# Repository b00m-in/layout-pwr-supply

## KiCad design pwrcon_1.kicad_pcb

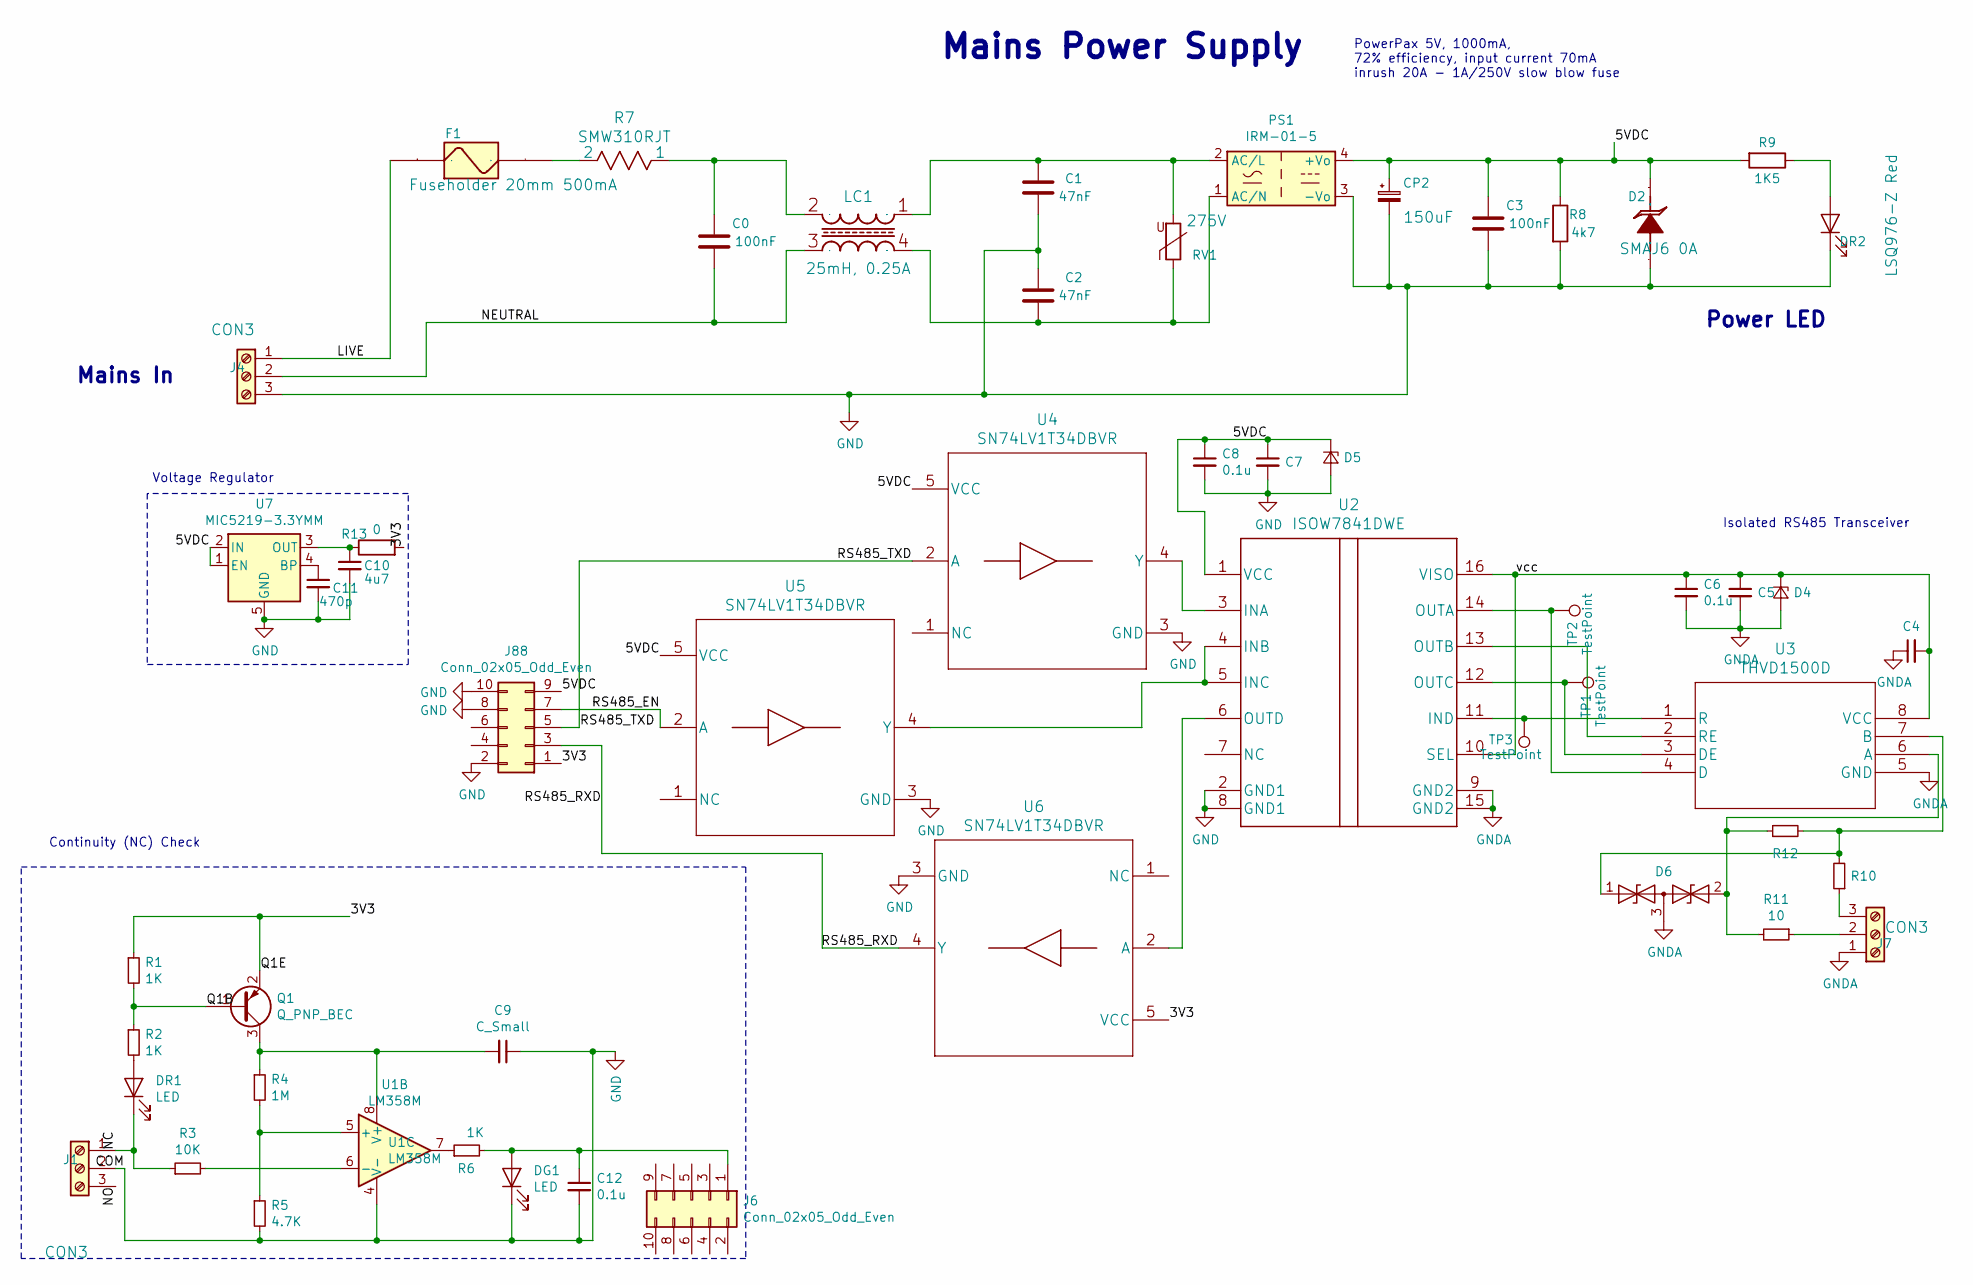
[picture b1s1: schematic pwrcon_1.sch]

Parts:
C0: 100nF; C_Rect_L18.0mm_W5.0mm_P15.00mm_FKS3_FKP3; PartNo ECQU2A104ML
C1, C2: 47nF; C_Rect_L10.0mm_W4.0mm_P7.50mm_MKS4; PartNo BFC233660473
C3: 100nF; C_0603_1608Metric_Pad1.05x0.95mm_HandSolder; MFG Part Num EMK107B7104KAHT
C4, C6, C8, C12: 0.1u; C_0603_1608Metric_Pad1.05x0.95mm_HandSolder; MFG Part Num C0603C104J4RACTU
C5, C7: 10u; C_0603_1608Metric_Pad1.05x0.95mm_HandSolder; MFG Part Num C0603C106M9PACTU
C9: C_Small; C_0603_1608Metric_Pad1.05x0.95mm_HandSolder; MFG Part Num ‎EMK107B7104KAHT‎
C10: 4u7; C_0603_1608Metric_Pad1.05x0.95mm_HandSolder; MFG Part Num F981A475MMA
C11: 470p; C_0603_1608Metric_Pad1.05x0.95mm_HandSolder; MFG Part Num ‎GRM033R61E471KA01D‎
CP2: 150uF; CP_EIA-7343-20_Kemet-V_Pad2.25x2.55mm_HandSolder; PartNo TRJD157K010R0150 / T495V157M010ATE150
D2: SMAJ6 0A; D_SMA; PartNo SMAJ6.0A
D4, D5: D_Zener_Small; D_SMB_Handsoldering; MFG Part Num 1SMB5919BT3G
D6: CDSOT23-SM712; SOT-23; MFG Part Num CDSOT23-SM712
DG1: LED; LED_0603_1608Metric_Pad1.05x0.95mm_HandSolder; MFG Part Num SML-D12M8WT86
DR1: LED; LED_0603_1608Metric_Pad1.05x0.95mm_HandSolder; MFG Part Num SML-D12V8WT86
DR2: LSQ976-Z Red; LED_0603_1608Metric_Pad1.05x0.95mm_HandSolder; PartNo LS Q976-NR-1
F1: Fuseholder 20mm 500mA; Fuseholder_Cylinder-5x20mm_Schurter_0031_8201_Horizontal_Op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; PartNo 0031.8201
J1, J4: CON3; PhoenixContact_MCV_1,5_3-G-5.08_1x03_P5.08mm_Vertical; MFG Part Num ED365/3
J6, J88: Conn_02x05_Odd_Even; PinSocket_2x05_P2.54mm_Vertical
J7: CON3; PhoenixContact_MCV_1,5_3-G-5.08_1x03_P5.08mm_Vertical; PartNo ED365/3
LC1: 25mH, 0.25A; choke_wurth_744862250; PartNo 744862250
PS1: IRM-01-5; Converter_ACDC_MeanWell_IRM-02-xx_THT; MFG Part Num IRM-01-5
Q1: Q_PNP_BEC; SOT-23_Handsoldering; MFG Part Num FMMT718
R1, R2, R6: 1K; R_0603_1608Metric; MFG Part Num ESR03EZPJ102
R3: 10K; R_0603_1608Metric
R4: 1M; R_0603_1608Metric; MFG Part Num RCS06031M00FKEA
R5: 4.7K; R_0603_1608Metric_Pad1.05x0.95mm_HandSolder; MFG Part Num ESR03EZPJ472
R7: SMW310RJT; MFG Part Num SMW310RJT
R8: 4k7; R_0805_2012Metric_Pad1.15x1.40mm_HandSolder; MFG Part Num ERJ-P06J472V
R9: 1K5; R_0603_1608Metric; MFG Part Num ESR03EZPJ152
R10, R11: 10; R_2512_6332Metric_Pad1.52x3.35mm_HandSolder; MFG Part Num CRCW251210R0FKEG
R12: 120; R_0603_1608Metric_Pad1.05x0.95mm_HandSolder; MFG Part Num CRCW0603120RJNEA
R13: 0; R_0603_1608Metric; MFG Part Num ESR03EZPJ152
RV1: 275V; RV_Disc_D7mm_W4mm_P5mm; PartNo 820572711
TP1, TP3: TestPoint; TestPoint_THTPad_D1.5mm_Drill0.7mm
TP2: TestPoint; TestPoint_Pad_D1.5mm
U1: LM358M; SOIC-8-1EP_3.9x4.9mm_P1.27mm_EP2.29x3mm; MFG Part Num LM358M/NOPB
U2: ISOW7841DWE; MFG Part Num ISOW7841D
U3: THVD1500D; MFG Part Num THVD1500DR
U4, U5, U6: SN74LV1T34DBVR; MFG Part Num SN74LV1T34DBVR
U7: MIC5219-3.3YMM; MSOP-8_3x3mm_P0.65mm; MFG Part Num MIC5219-3.3YMM

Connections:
/3V3: J88.1, Q1.2 (E), R1.1, R13.2, U6.5 (VCC)
/5VDC: C3.2, C7.1, C8.1, CP2.1, D2.1 (CATHODE), D5.1 (K), J88.9, PS1.4 (+Vo), R8.1, R9.2, U2.1 (VCC), U4.5 (VCC), U5.5 (VCC), U7.1 (EN), U7.2 (IN)
/LIVE: F1.1, J4.1
/NC: DR1.1 (K), J1.1, R3.1
/NEUTRAL: C0.1, J4.2, LC1.3
/Q1B: Q1.1 (B), R1.2, R2.1
/RS485_EN: J88.7, U5.2 (A)
/RS485_RXD: J88.3, U6.4 (Y)
/RS485_TXD: J88.5, U4.2 (A)
/vcc: C4.2, C5.1, C6.1, D4.1 (K), U2.10 (SEL), U2.16 (VISO), U3.8 (VCC)
GND: C1.1, C2.2, C3.1, C7.2, C8.2, C9.1, C10.2, C11.2, C12.2, CP2.2, D2.2 (ANODE), D5.2 (A), DG1.1 (K), DR2.1 (K), J1.2, J4.3, J88.2, J88.8, J88.10, PS1.3 (-Vo), R5.2, R8.2, U1.4 (V-), U2.2 (GND1), U2.8 (GND1), U4.3 (GND), U5.3 (GND), U6.3 (GND), U7.5 (GND), U7.6 (GND), U7.7 (GND), U7.8 (GND)
GNDA: C4.1, C5.2, C6.2, D4.2 (A), D6.3 (common), J7.1, U2.9 (GND2), U2.15 (GND2), U3.5 (GND)
unnamed: C0.2, LC1.2, R7.1
unnamed: C1.2, LC1.1, PS1.2 (AC/L), RV1.2
unnamed: C2.1, LC1.4, PS1.1 (AC/N), RV1.1
unnamed: C9.2, Q1.3 (C), R4.1, U1.8 (V+)
unnamed: C10.1, R13.1, U7.3 (OUT)
unnamed: C11.1, U7.4 (BP)
unnamed: C12.1, DG1.2 (A), J6.1, R6.2
unnamed: D6.1 (A1), R10.2, R12.2, U3.7 (B)
unnamed: D6.2 (A2), R11.2, R12.1, U3.6 (A)
unnamed: DR1.2 (A), R2.2
unnamed: DR2.2 (A), R9.1
unnamed: F1.2, R7.2
unnamed: J7.2, R11.1
unnamed: J7.3, R10.1
unnamed: R3.2, U1.6 (-)
unnamed: R4.2, R5.1, U1.5 (+)
unnamed: R6.1, U1.7
unnamed: TP1.1, U2.12 (OUTC), U3.3 (DE)
unnamed: TP2.1, U2.14 (OUTA), U3.4 (D)
unnamed: TP3.1, U2.11 (IND), U3.1 (R)
unnamed: U2.3 (INA), U4.4 (Y)
unnamed: U2.4 (INB), U2.5 (INC), U5.4 (Y)
unnamed: U2.6 (OUTD), U6.2 (A)
unnamed: U2.13 (OUTB), U3.2 (RE)

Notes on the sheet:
Mains Power Supply
PowerPax 5V, 1000mA, 72% efficiency, input current 70mA inrush 20A - 1A/250V slow blow fuse
Mains In
Isolated RS485 Transceiver
Power LED
Voltage Regulator
Continuity (NC) Check

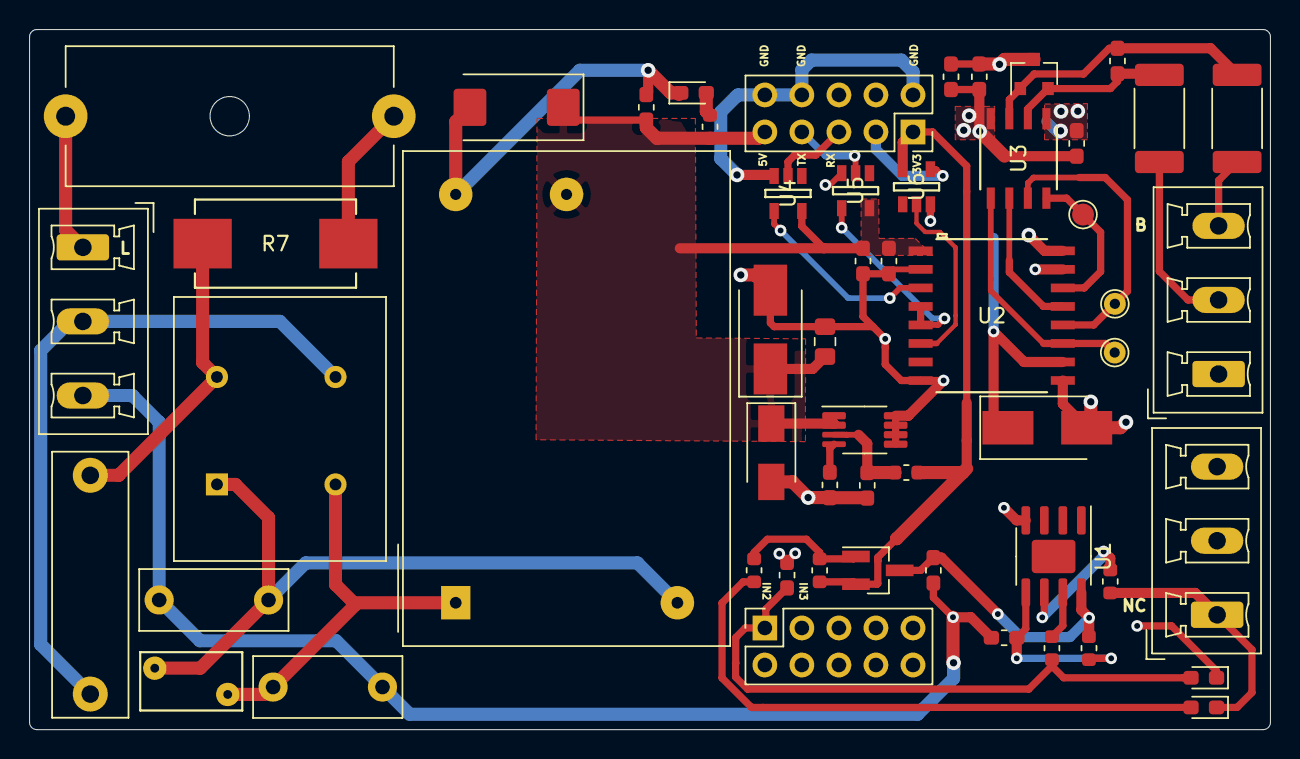
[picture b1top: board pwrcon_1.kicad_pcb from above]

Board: 2 copper layers, 85.1 x 48.0 mm, 54 parts (0 on the bottom side), 36 nets.

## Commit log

2020-10-06 Added missing 5VDC connection to isolator (isow7841dwe) and created new net vcc between isolator and esd/transceiver(thvd1500d). Changed layout.
2020-10-12 Headers should now match cc3220modasf commit d3c2dc17dd42c882b5c02795b58cb5e5026f240b
2021-05-10 State at time of 2021-11-25 Aisler order
2021-05-10 Reduced shot/image resolution

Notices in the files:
parts and their libraries:
Copyright 2016 Accelerated Designs. All rights reserved.
